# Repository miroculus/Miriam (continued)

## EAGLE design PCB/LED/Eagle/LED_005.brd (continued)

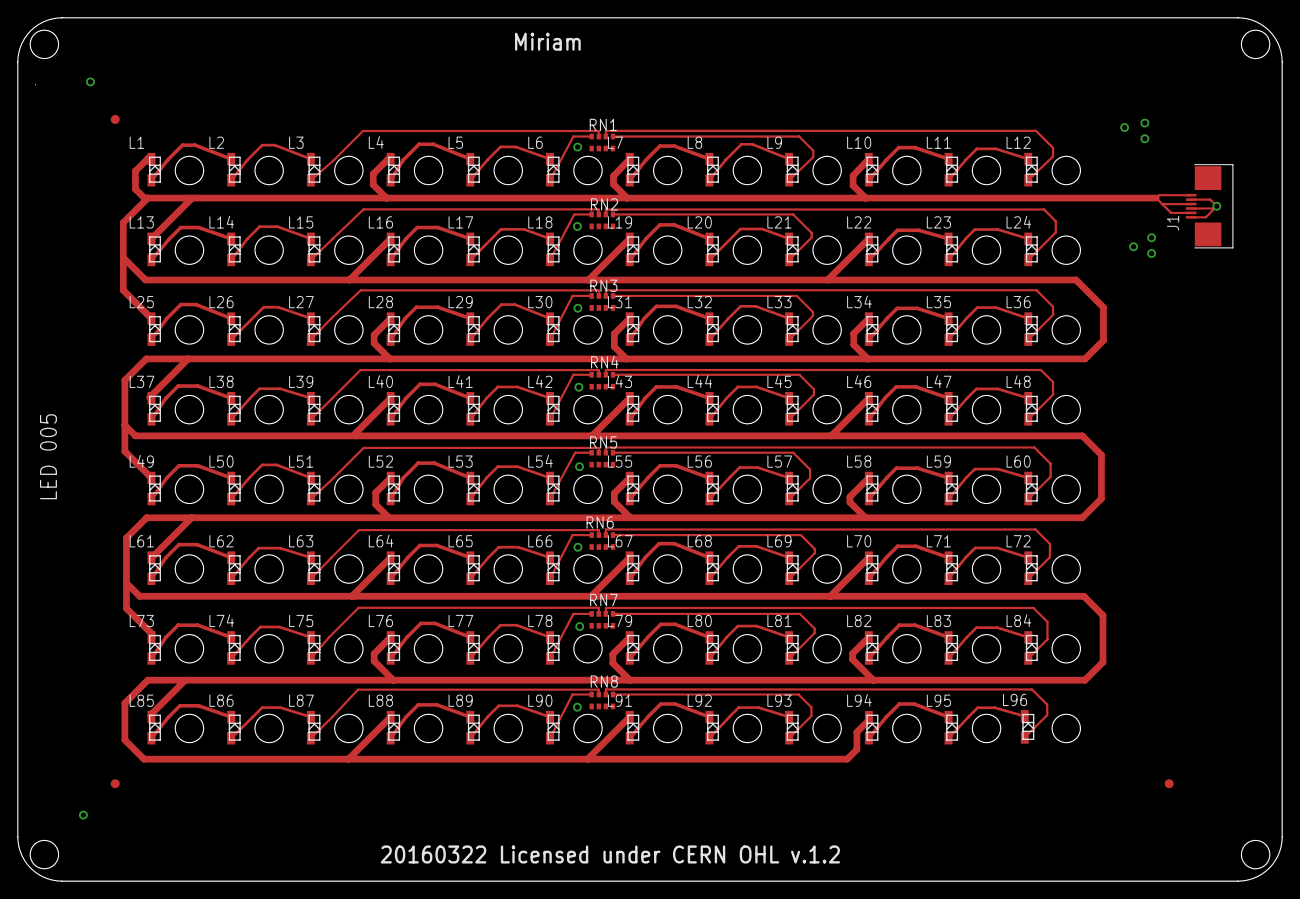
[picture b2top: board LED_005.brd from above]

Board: 2 copper layers, 142.8 x 97.5 mm, 108 parts (0 on the bottom side), 98 nets.

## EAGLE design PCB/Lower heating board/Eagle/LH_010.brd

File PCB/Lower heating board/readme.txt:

The used board is aluminum

- 1oz copper
- 1.6 mm thick
- Leadfree HAL
- Black soldermask
- White silkscreen

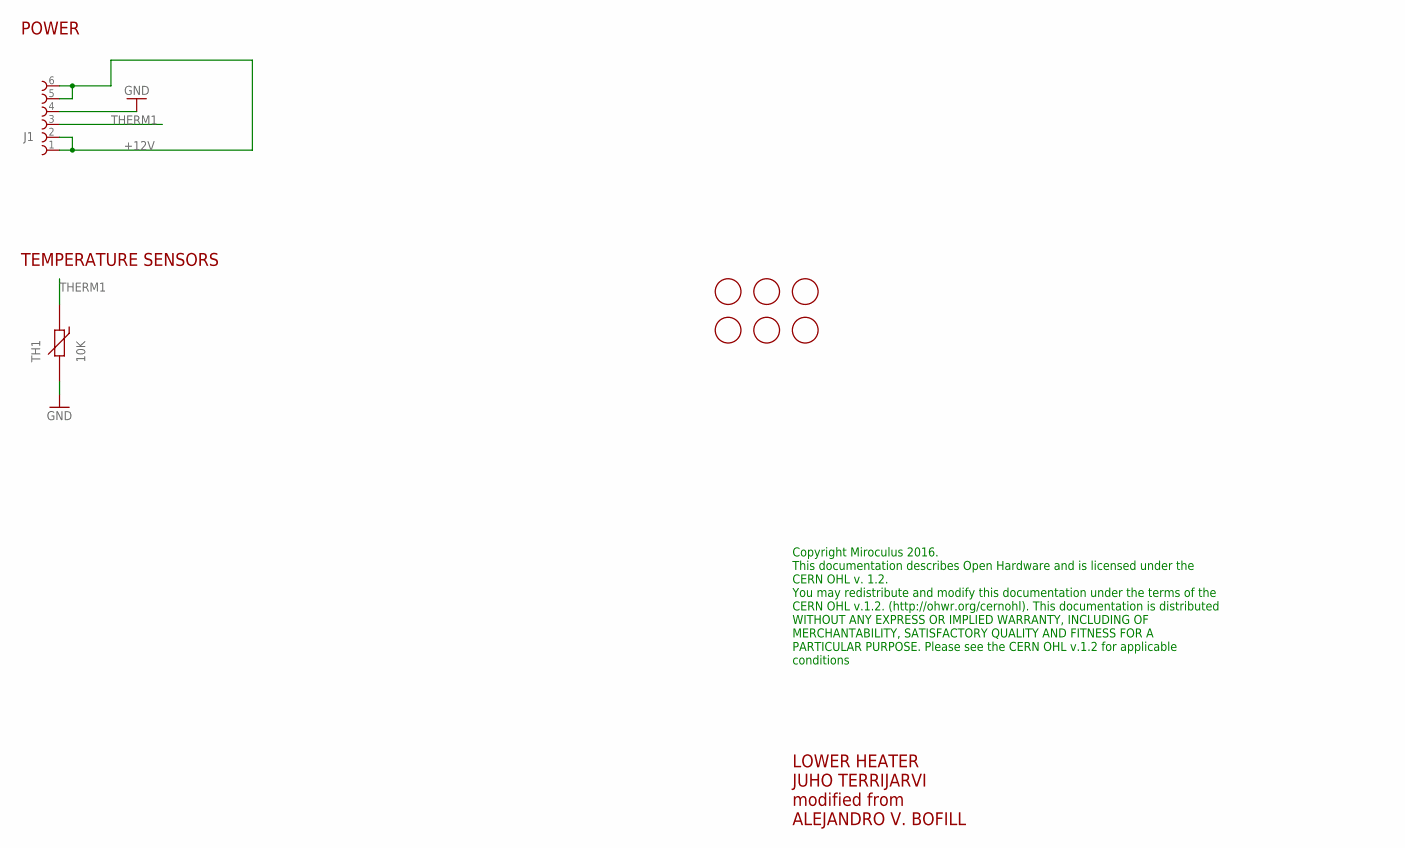
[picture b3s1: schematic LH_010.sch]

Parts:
FD1, FD2, FD3, FD4, FD5, FD6: FIDUCIALMOUNT; FIDUCIA-MOUNT
J1: 68710614522
TH1: 10K; THERMISTOR_SMD_0603

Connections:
+12V: J1.1, J1.2, J1.5, J1.6
GND: J1.4, TH1.2
THERM1: J1.3, TH1.1

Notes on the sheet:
LOWER HEATER JUHO TERRIJARVI modified from ALEJANDRO V. BOFILL
POWER
TEMPERATURE SENSORS
Copyright Miroculus 2016. This documentation describes Open Hardware and is licensed under the CERN OHL v. 1.2. You may redistribute and modify this documentation under the terms of the CERN OHL v.1.2. (http://ohwr.org/cernohl). This documentation is distributed WITHOUT ANY EXPRESS OR IMPLIED WARRA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

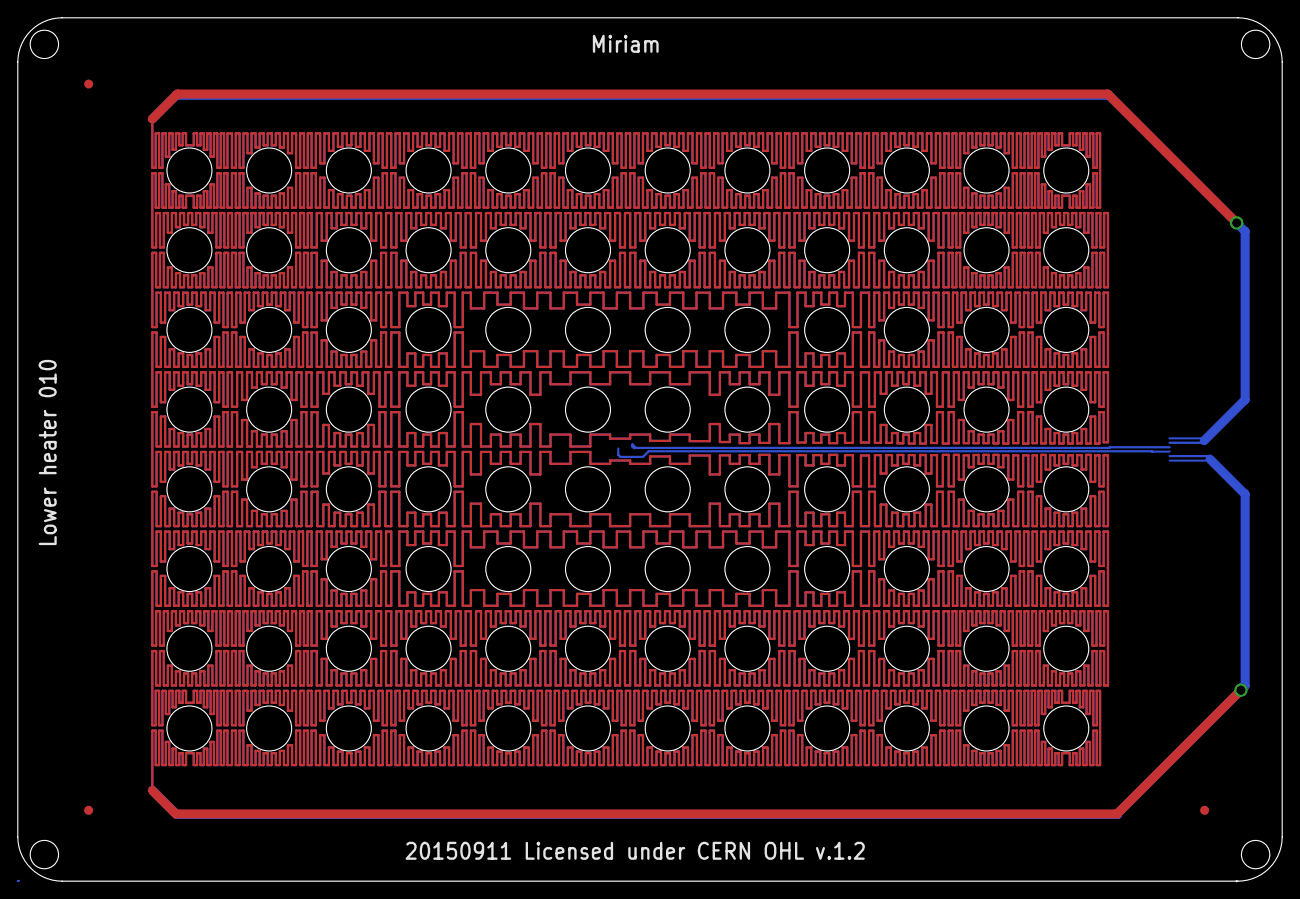
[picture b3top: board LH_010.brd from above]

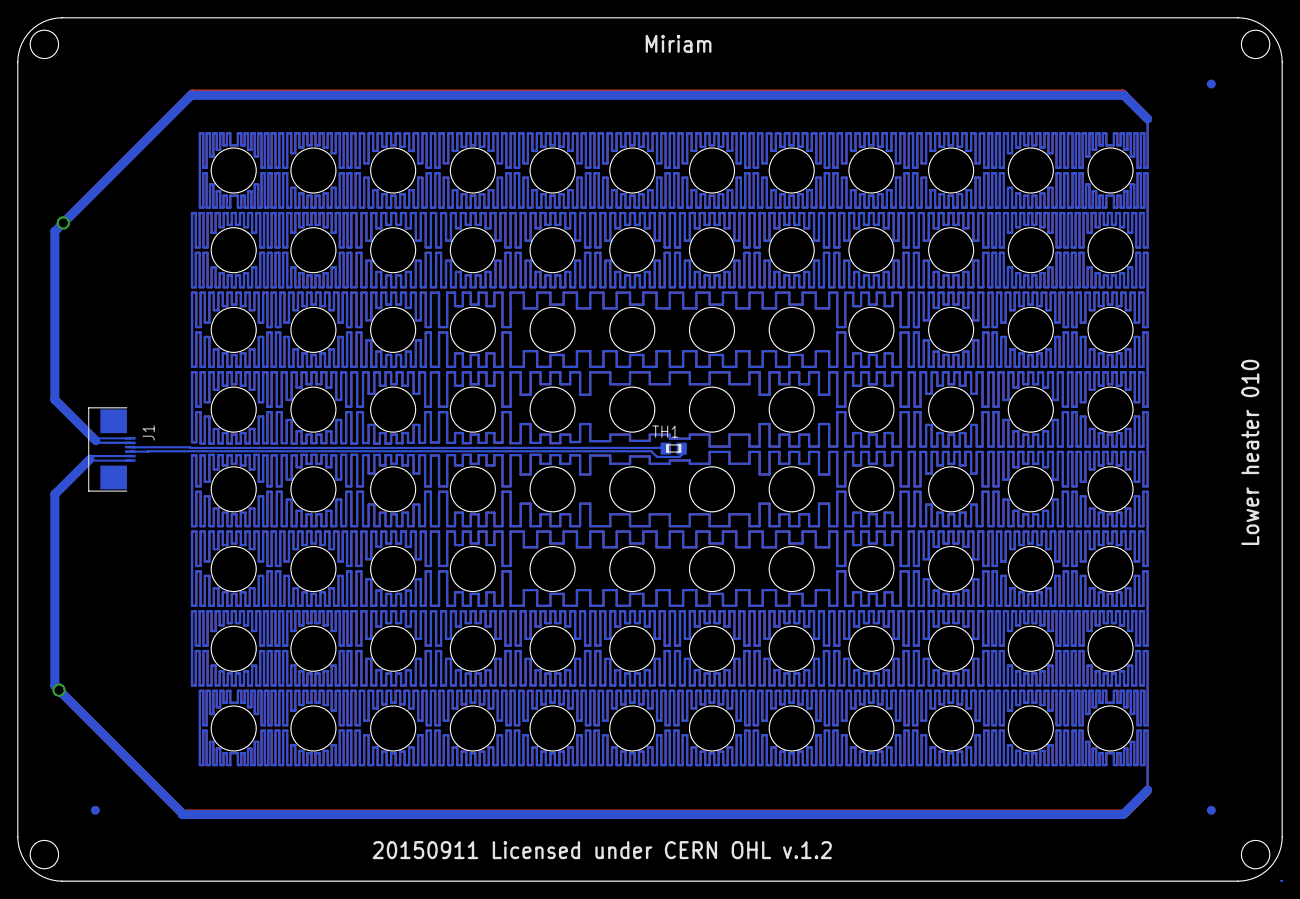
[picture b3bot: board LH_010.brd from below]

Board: 2 copper layers, 142.8 x 97.5 mm, 8 parts (5 on the bottom side), 3 nets.

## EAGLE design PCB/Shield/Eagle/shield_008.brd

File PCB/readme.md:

# PCBs

The PCBs have been drawn with Eagle software 7.3.0

PCB order details are in separate readme files in correct subfolders.

The Bills of material can be found under folder BOM. Datasheets of the main components are under folder Components.

Some of the component layouts can be found under Library folder that houses the Eagle .lbrs

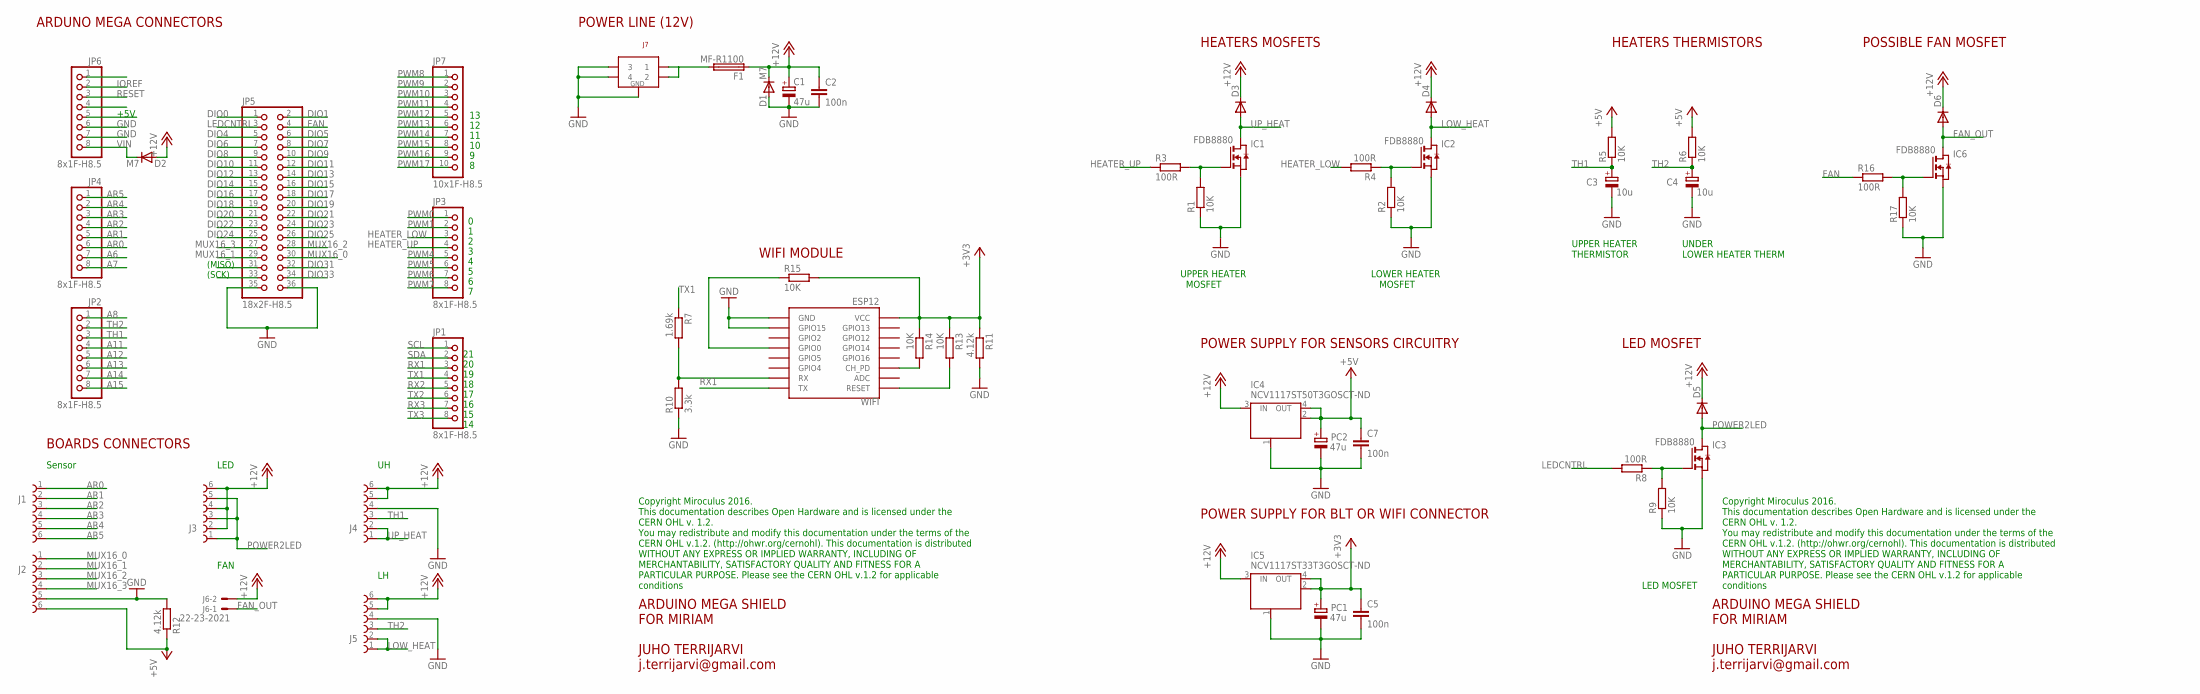
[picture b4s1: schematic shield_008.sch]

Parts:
C1: 47u; PANASONIC_D
C2, C5, C7: 100n; C0603
C3, C4: 10u; A/3216-18R
D1, D2: M7; SMB
D3, D4, D5, D6: RGL34A; DO-213AA_DIODE
F1: MF-R1100; LITTLEFUSE; FARNELL 1652183
IC1, IC2, IC3, IC6: FDB8880
IC4: NCV1117ST50T3GOSCT-ND; SOT223
IC5: NCV1117ST33T3GOSCT-ND; SOT223
J1, J2, J3, J4, J5: 68710614522
J6: 22-23-2021
J7: KPJX-4S-S
JP1, JP2, JP3, JP4, JP6: 8x1F-H8.5; 1X08
JP5: 18x2F-H8.5; 2X18
JP7: 10x1F-H8.5; 1X10
PC1, PC2: 47u; PANASONIC_D
R1, R2, R5, R6, R9, R13, R14, R15, R17: 10K; R0603
R3, R4, R8, R16: 100R; R0603
R7: 1.69k; R0603
R10: 3.3k; R0603
R11, R12: 4.12k; R0603
WIFI: ESP12

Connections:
+3V3: C5.1, IC5.2 (OUT), IC5.4 (OUT), PC1.+, R11.1, R13.1, R14.1, R15.2, WIFI.VCC
+5V: C7.1, IC4.2 (OUT), IC4.4 (OUT), J2.6, PC2.+, R5.2, R6.2, R12.1
+12V: C1.+, C2.1, D1.C, D2.A, D3.P$2 (C), D4.P$2 (C), D5.P$2 (C), D6.P$2 (C), F1.1, IC4.3 (IN), IC5.3 (IN), J3.2, J3.4, J3.6, J4.5, J4.6, J5.5, J5.6, J6.2
A6: JP4.7
A7: JP4.8
A8: JP2.1
A11: JP2.4
A12: JP2.5
A13: JP2.6
A14: JP2.7
A15: JP2.8
AR0: J1.1, JP4.6
AR1: J1.2, JP4.5
AR2: J1.3, JP4.4
AR3: J1.4, JP4.3
AR4: J1.5, JP4.2
AR5: J1.6, JP4.1
DIO0: JP5.1
DIO1: JP5.2
DIO4: JP5.5
DIO5: JP5.6
DIO6: JP5.7
DIO7: JP5.8
DIO8: JP5.9
DIO9: JP5.10
DIO10: JP5.11
DIO11: JP5.12
DIO12: JP5.13
DIO13: JP5.14
DIO14: JP5.15
DIO15: JP5.16
DIO16: JP5.17
DIO17: JP5.18
DIO18: JP5.19
DIO19: JP5.20
DIO20: JP5.21
DIO21: JP5.22
DIO22: JP5.23
DIO23: JP5.24
DIO24: JP5.25
DIO25: JP5.26
DIO30: JP5.31
DIO31: JP5.32
DIO32: JP5.33
DIO33: JP5.34
FAN: JP5.4, R16.1
FAN_OUT: D6.P$1 (A), IC6.2 (D), J6.1
GND: C1.-, C2.2, C3.-, C4.-, C5.2, C7.2, D1.A, IC1.3 (S), IC2.3 (S), IC3.3 (S), IC4.1 (GND/ADJ), IC5.1 (GND/ADJ), IC6.3 (S), J2.5, J4.4, J5.4, J7.P$3 (3), J7.P$4 (4), J7.P$5 (G), J7.P$6 (G), J7.P$7 (G), JP5.35, JP5.36, JP6.6, JP6.7, PC1.-, PC2.-, R1.1, R2.1, R9.1, R10.1, R11.2, R12.2, R17.1, WIFI.GND, WIFI.GPIO15
HEATER_LOW: JP3.3, R4.2
HEATER_UP: JP3.4, R3.1
IOREF: JP6.2
LEDCNTRL: JP5.3, R8.2
LOW_HEAT: D4.P$1 (A), IC2.2 (D), J5.1, J5.2
MUX16_0: J2.1, JP5.30
MUX16_1: J2.2, JP5.29
MUX16_2: J2.3, JP5.28
MUX16_3: J2.4, JP5.27
unnamed: IC3.1 (G), R8.1, R9.2
unnamed: R7.2, R10.2, WIFI.RX
unnamed: R13.2, WIFI.RESET
unnamed: R14.2, WIFI.CH_PD
unnamed: R15.1, WIFI.GPIO0
unnamed: F1.2, J7.P$1 (1), J7.P$2 (2)
unnamed: IC6.1 (G), R16.2, R17.2
unnamed: IC1.1 (G), R1.2, R3.2
unnamed: IC2.1 (G), R2.2, R4.1
POWER2LED: D5.P$1 (A), IC3.2 (D), J3.1, J3.3, J3.5
PWM0: JP3.1
PWM1: JP3.2
PWM4: JP3.5
PWM5: JP3.6
PWM6: JP3.7
PWM7: JP3.8
PWM8: JP7.1
PWM9: JP7.2
PWM10: JP7.3
PWM11: JP7.4
PWM12: JP7.5
PWM13: JP7.6
PWM14: JP7.7
PWM15: JP7.8
PWM16: JP7.9
PWM17: JP7.10
RESET: JP6.3
RX1: JP1.3, WIFI.TX
RX2: JP1.5
RX3: JP1.7
SCL: JP1.1
SDA: JP1.2
TH1: C3.+, J4.3, JP2.3, R5.1
TH2: C4.+, J5.3, JP2.2, R6.1
TX1: JP1.4, R7.1
TX2: JP1.6
TX3: JP1.8
UP_HEAT: D3.P$1 (A), IC1.2 (D), J4.1, J4.2
VIN: D2.C, JP6.8

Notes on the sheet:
(SCK)
(MISO)
ARDUNO MEGA CONNECTORS
ARDUINO MEGA SHIELD FOR MIRIAM JUHO TERRIJARVI j.terrijarvi@gmail.com
POWER LINE (12V)
BOARDS CONNECTORS
HEATERS MOSFETS
HEATERS THERMISTORS
UPPER HEATER THERMISTOR
UNDER LOWER HEATER THERM
UPPER HEATER MOSFET
LOWER HEATER MOSFET
WIFI MODULE
+5V
POWER SUPPLY FOR SENSORS CIRCUITRY
LED MOSFET
POWER SUPPLY FOR BLT OR WIFI CONNECTOR
Copyright Miroculus 2016. This documentation describes Open Hardware and is licensed under the CERN OHL v. 1.2. You may redistribute and modify this documentation under the terms of the CERN OHL v.1.2. (http://ohwr.org/cernohl). This documentation is distributed WITHOUT ANY EXPRESS OR IMPLIED WARRA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
Sensor
LED
POSSIBLE FAN MOSFET
FAN

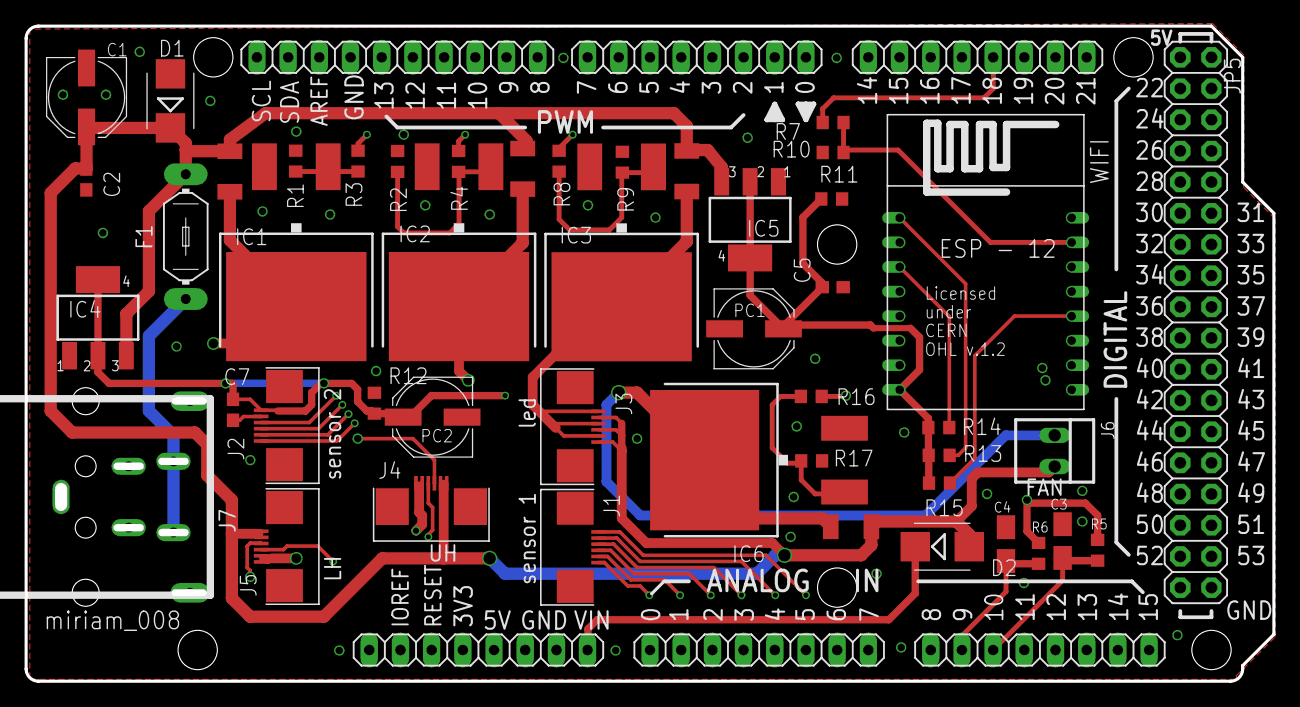
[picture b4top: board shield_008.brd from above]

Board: 4 copper layers, 101.6 x 53.3 mm, 53 parts (0 on the bottom side), 36 nets.

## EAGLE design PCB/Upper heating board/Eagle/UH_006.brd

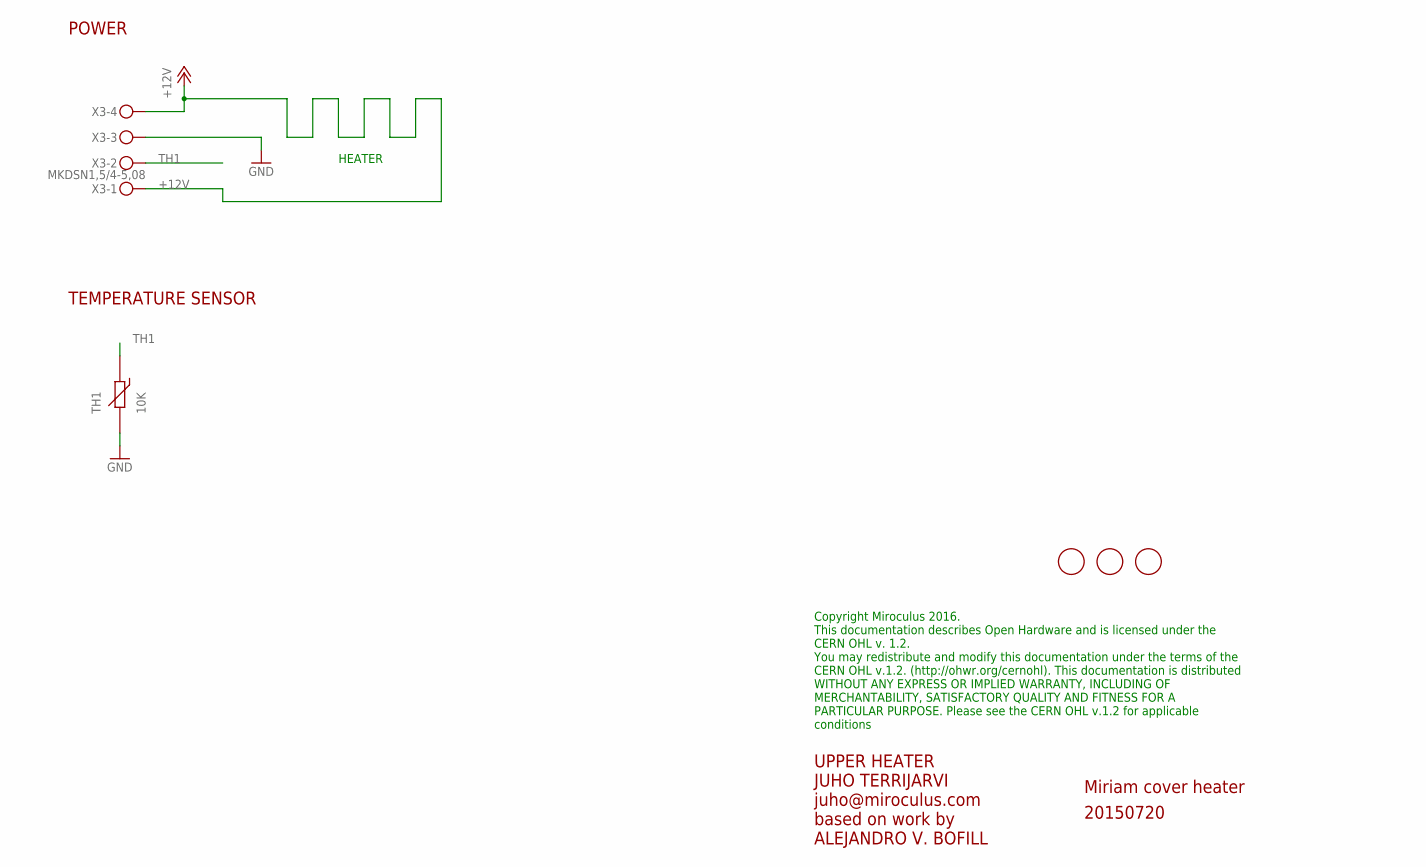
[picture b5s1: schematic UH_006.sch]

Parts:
FD1, FD2, FD3: FIDUCIALMOUNT; FIDUCIA-MOUNT
TH1: 10K; THERMISTOR_SMD_0603
X3: MKDSN1,5/4-5,08

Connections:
+12V: X3.1, X3.4
GND: TH1.2, X3.3
TH1: TH1.1, X3.2

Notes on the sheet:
POWER
UPPER HEATER JUHO TERRIJARVI juho@miroculus.com based on work by ALEJANDRO V. BOFILL
HEATER
TEMPERATURE SENSOR
Miriam cover heater
20150720
Copyright Miroculus 2016. This documentation describes Open Hardware and is licensed under the CERN OHL v. 1.2. You may redistribute and modify this documentation under the terms of the CERN OHL v.1.2. (http://ohwr.org/cernohl). This documentation is distributed WITHOUT ANY EXPRESS OR IMPLIED WARRA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

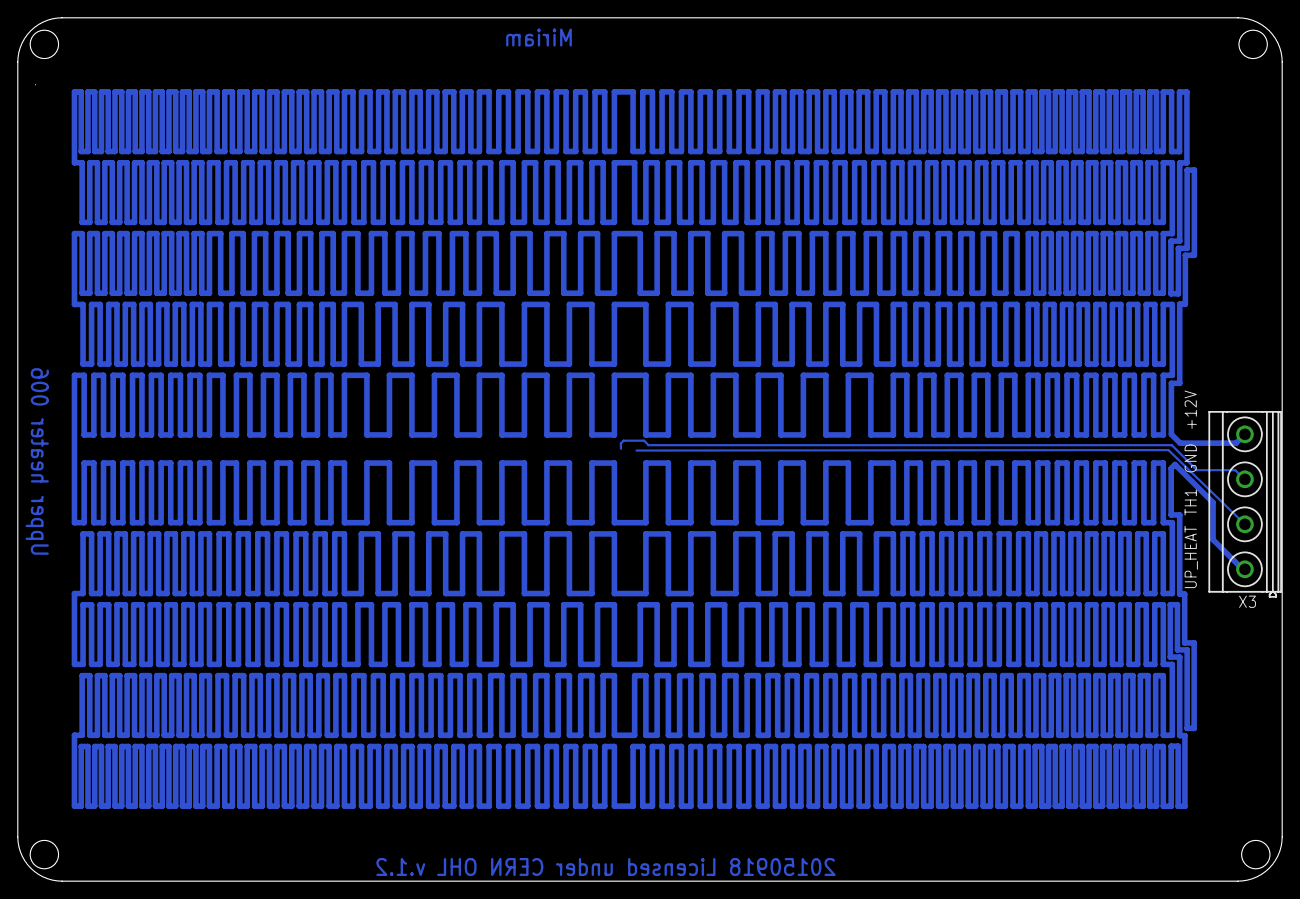
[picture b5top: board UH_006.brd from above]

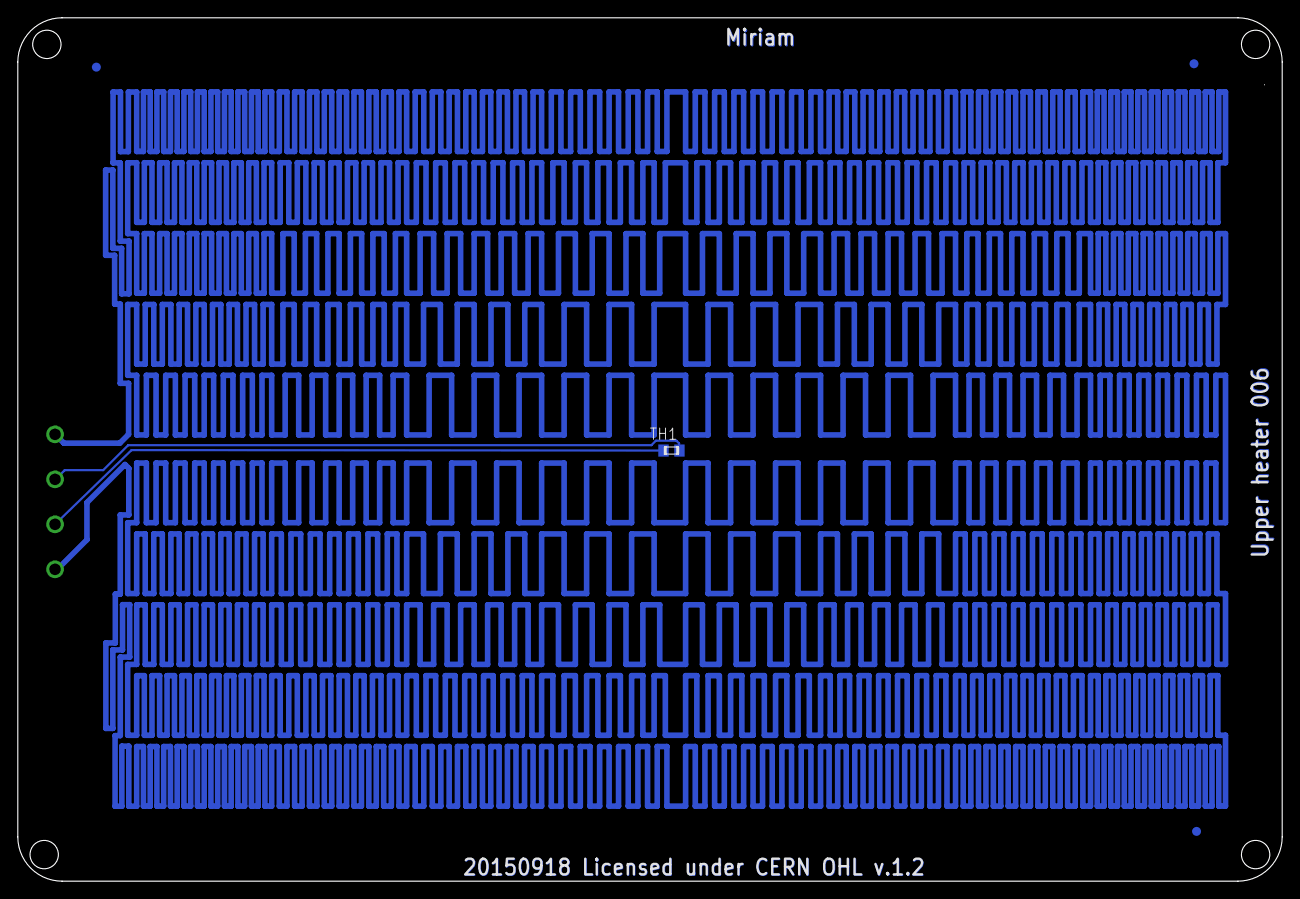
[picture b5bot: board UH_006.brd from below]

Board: 2 copper layers, 142.8 x 97.5 mm, 5 parts (4 on the bottom side), 3 nets.

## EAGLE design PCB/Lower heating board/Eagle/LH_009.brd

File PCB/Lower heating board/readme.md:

# LH_010

- material aluminum
- 2 layer
- single sided assembly
- 1oz copper
- 1.6 mm thick
- Leadfree HAL
- Black soldermask
- White silkscreen

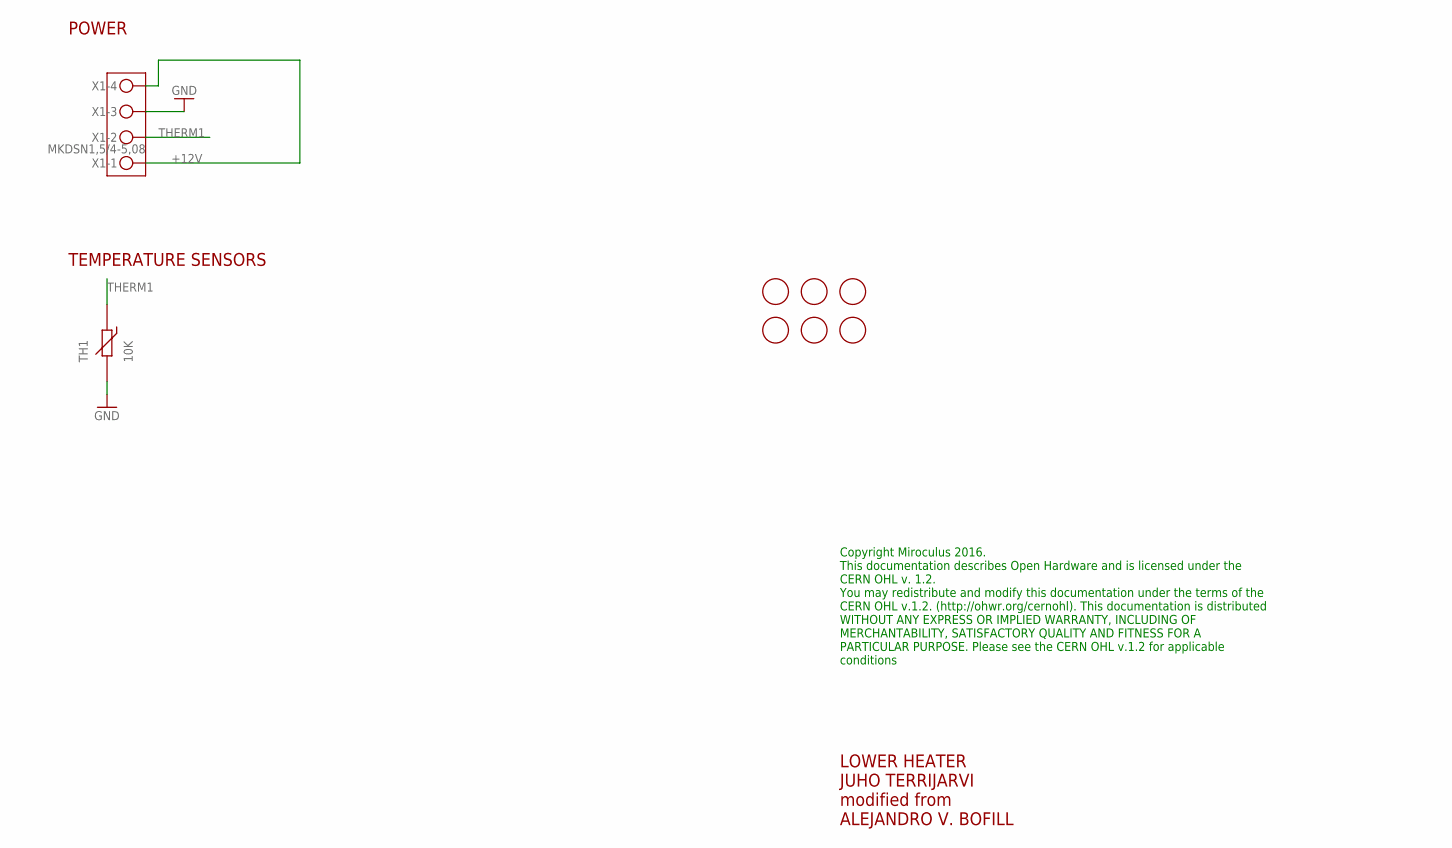
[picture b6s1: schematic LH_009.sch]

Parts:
FD1, FD2, FD3, FD4, FD5, FD6: FIDUCIALMOUNT; FIDUCIA-MOUNT
TH1: 10K; THERMISTOR_SMD_0603
X1: MKDSN1,5/4-5,08

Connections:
+12V: X1.1, X1.4
GND: TH1.2, X1.3
THERM1: TH1.1, X1.2

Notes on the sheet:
LOWER HEATER JUHO TERRIJARVI modified from ALEJANDRO V. BOFILL
POWER
TEMPERATURE SENSORS
Copyright Miroculus 2016. This documentation describes Open Hardware and is licensed under the CERN OHL v. 1.2. You may redistribute and modify this documentation under the terms of the CERN OHL v.1.2. (http://ohwr.org/cernohl). This documentation is distributed WITHOUT ANY EXPRESS OR IMPLIED WARRA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

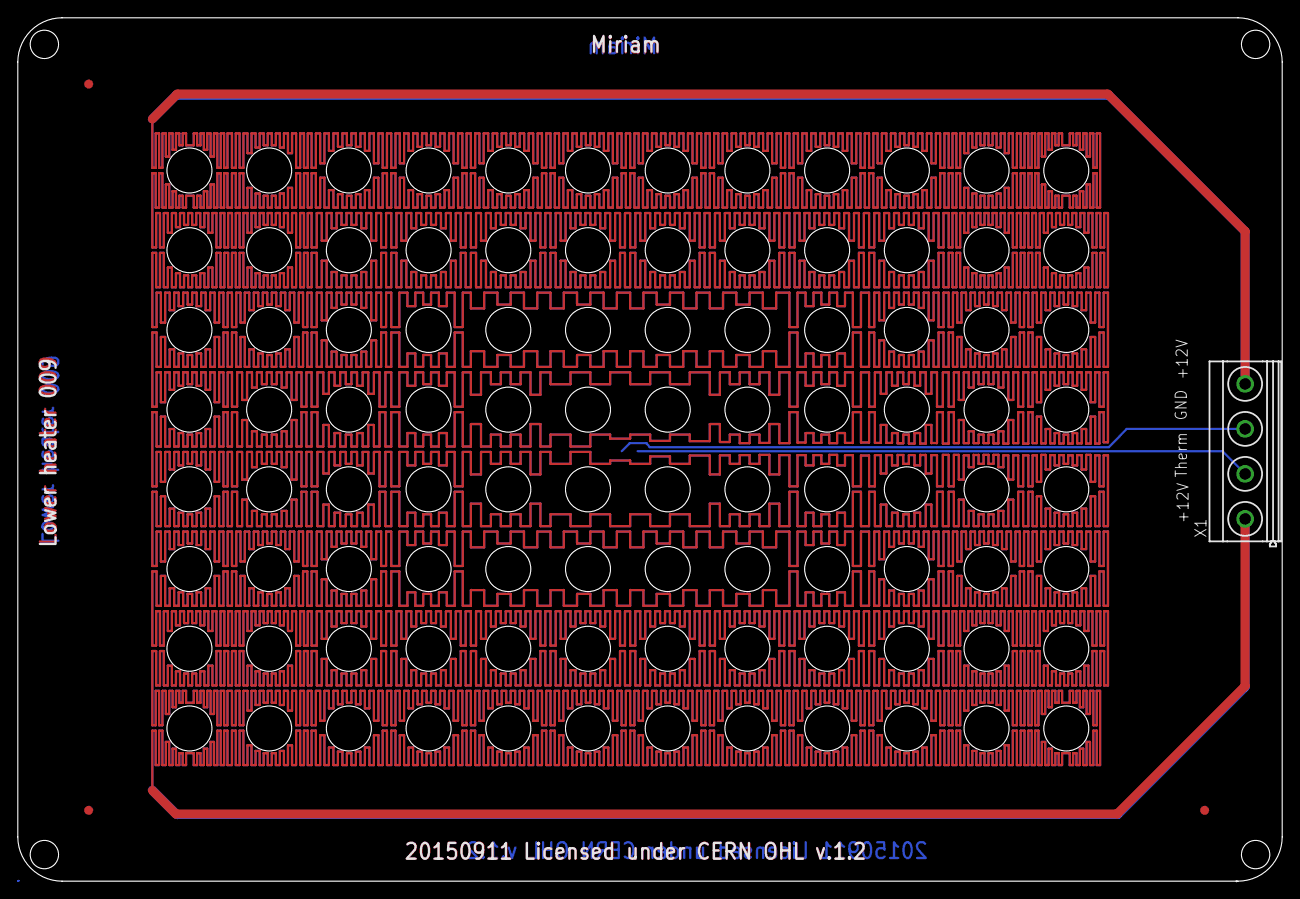
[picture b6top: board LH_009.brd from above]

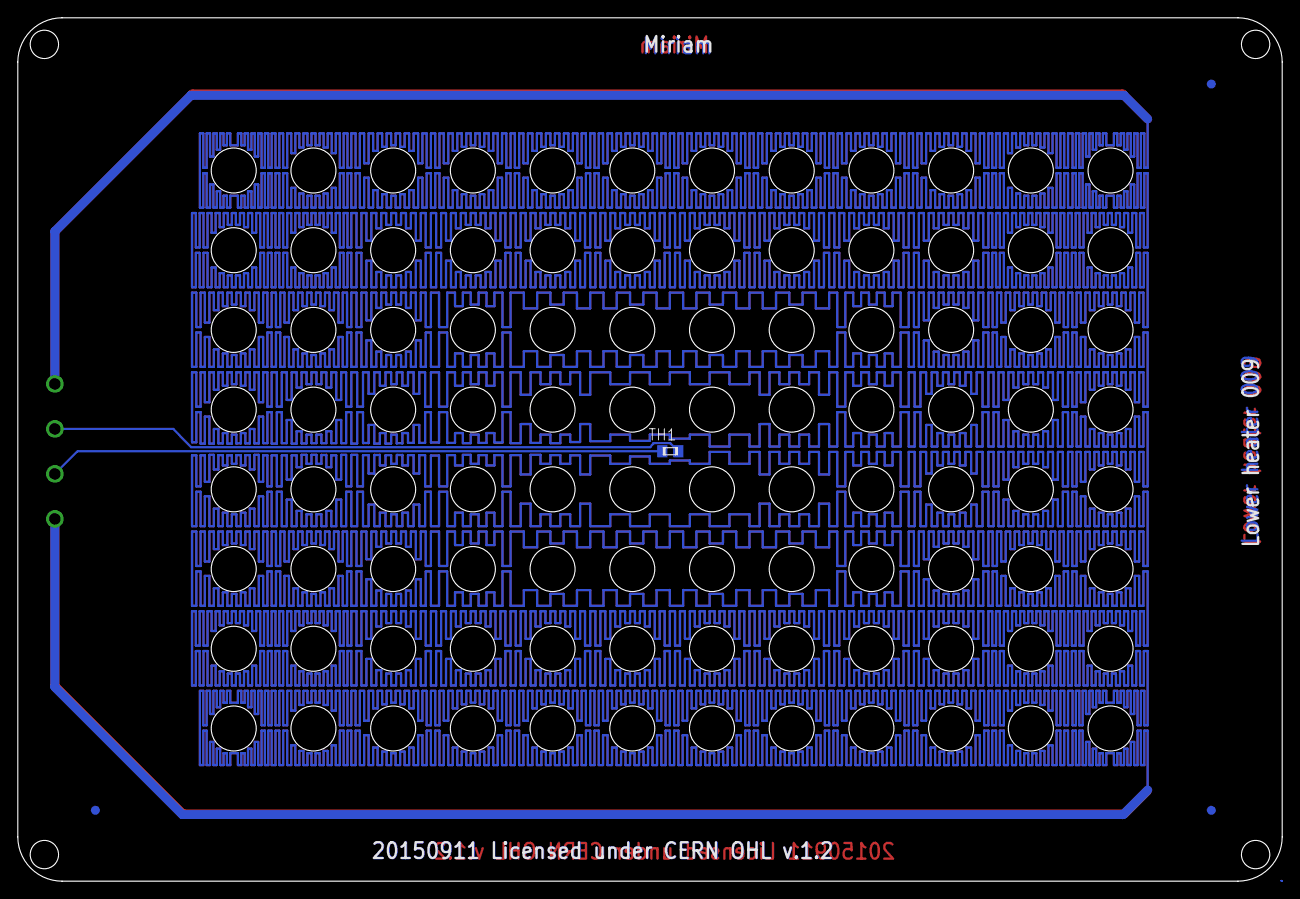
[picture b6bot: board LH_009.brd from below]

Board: 2 copper layers, 142.8 x 97.5 mm, 8 parts (4 on the bottom side), 3 nets.

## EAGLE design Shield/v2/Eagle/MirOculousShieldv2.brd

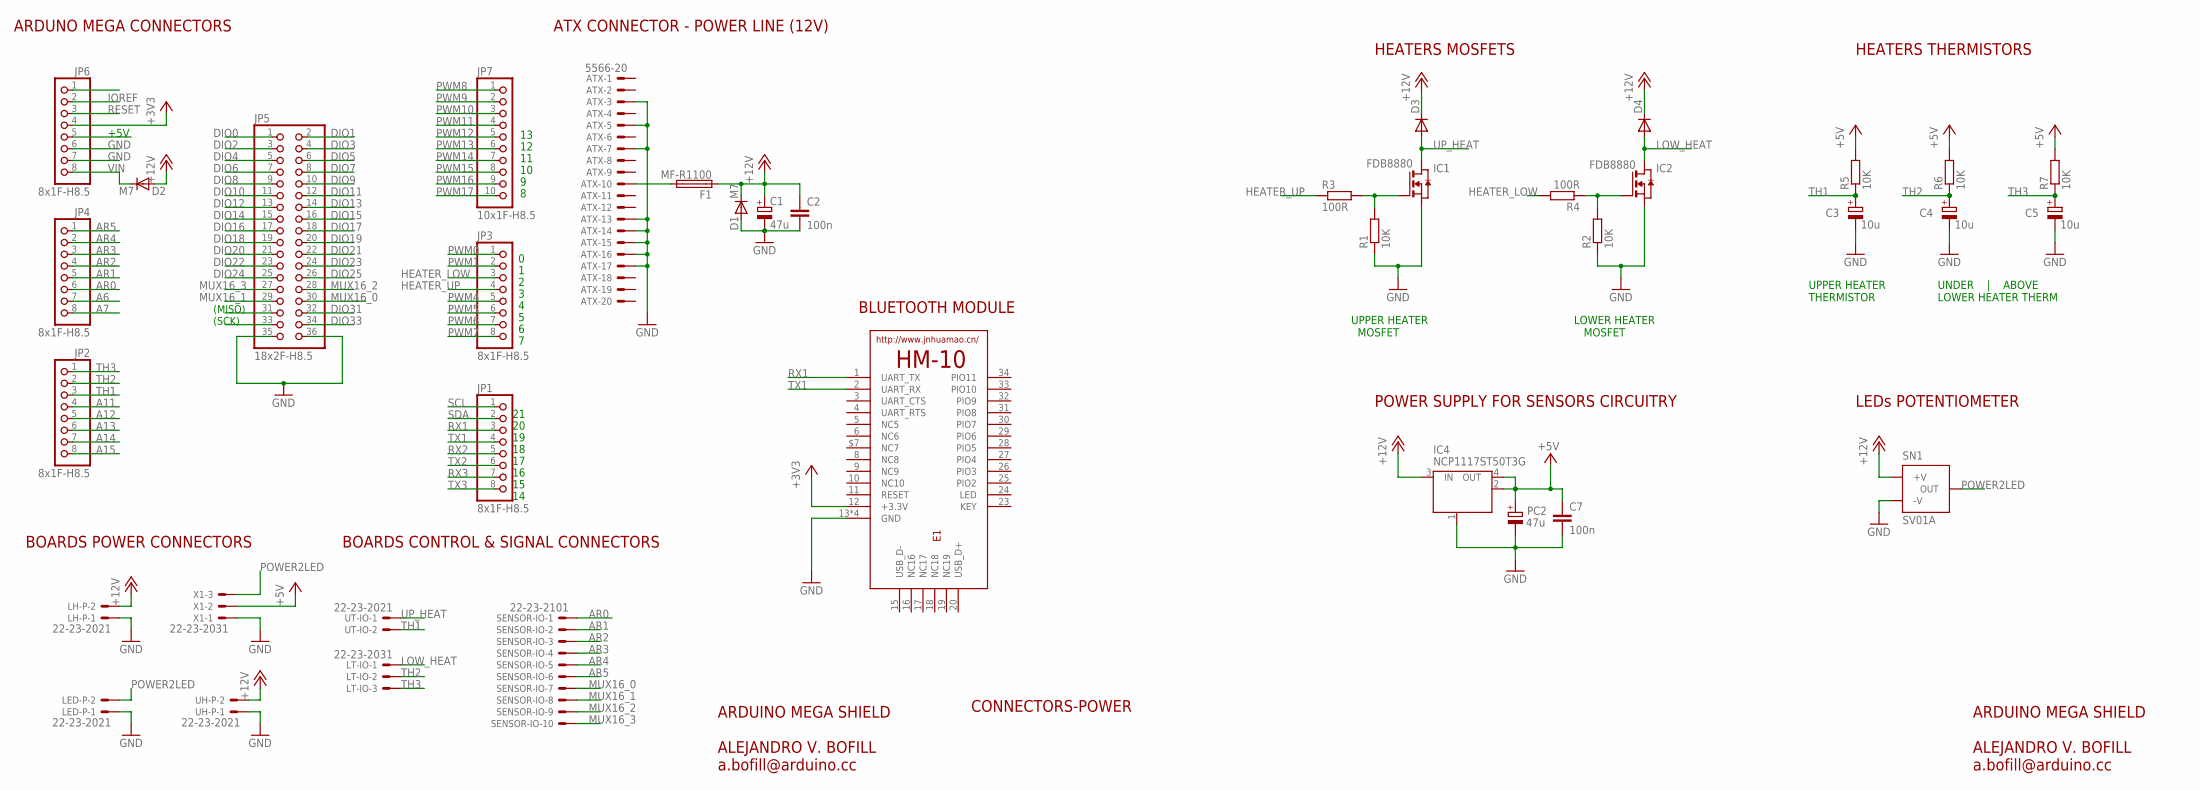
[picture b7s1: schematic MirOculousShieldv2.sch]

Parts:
ATX: 5566-20
C1: 47u; PANASONIC_D
C2, C7: 100n; C0603
C3, C4, C5: 10u; A/3216-18R
D1, D2: M7; SMB
D3, D4: RGL34A; DO-213AA_DIODE
E1: HM-10-BOARD; 26.9X13X2.2_BOARD
F1: MF-R1100; LITTLEFUSE; FARNELL 1652183
IC1, IC2: FDB8880
IC4: NCP1117ST50T3G; SOT223
JP1, JP2, JP3, JP4, JP6: 8x1F-H8.5; 1X08
JP5: 18x2F-H8.5; 2X18
JP7: 10x1F-H8.5; 1X10
LED-P: 22-23-2021
LH-P: 22-23-2021
LT-IO: 22-23-2031
PC2: 47u; PANASONIC_D
R1, R2, R5, R6, R7: 10K; R0603
R3, R4: 100R; R0603
SENSOR-IO: 22-23-2101
SN1: SV01A
UH-P: 22-23-2021
UT-IO: 22-23-2021
X1: 22-23-2031

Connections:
+3V3: E1.12 (+3.3V), JP6.4
+5V: C7.1, IC4.2 (OUT), IC4.4 (OUT), PC2.+, R5.2, R6.2, R7.2, X1.2
+12V: C1.+, C2.1, D1.C, D2.A, D3.P$2 (C), D4.P$2 (C), F1.1, IC4.3 (IN), LH-P.2, SN1.3 (+V), UH-P.2
A6: JP4.7
A7: JP4.8
A11: JP2.4
A12: JP2.5
A13: JP2.6
A14: JP2.7
A15: JP2.8
AR0: JP4.6, SENSOR-IO.1
AR1: JP4.5, SENSOR-IO.2
AR2: JP4.4, SENSOR-IO.3
AR3: JP4.3, SENSOR-IO.4
AR4: JP4.2, SENSOR-IO.5
AR5: JP4.1, SENSOR-IO.6
DIO0: JP5.1
DIO1: JP5.2
DIO2: JP5.3
DIO3: JP5.4
DIO4: JP5.5
DIO5: JP5.6
DIO6: JP5.7
DIO7: JP5.8
DIO8: JP5.9
DIO9: JP5.10
DIO10: JP5.11
DIO11: JP5.12
DIO12: JP5.13
DIO13: JP5.14
DIO14: JP5.15
DIO15: JP5.16
DIO16: JP5.17
DIO17: JP5.18
DIO18: JP5.19
DIO19: JP5.20
DIO20: JP5.21
DIO21: JP5.22
DIO22: JP5.23
DIO23: JP5.24
DIO24: JP5.25
DIO25: JP5.26
DIO30: JP5.31
DIO31: JP5.32
DIO32: JP5.33
DIO33: JP5.34
GND: ATX.3, ATX.5, ATX.7, ATX.13, ATX.14, ATX.15, ATX.16, ATX.17, C1.-, C2.2, C3.-, C4.-, C5.-, C7.2, D1.A, E1.13 (GND), E1.14 (GND), E1.21 (GND), E1.22 (GND), IC1.3 (S), IC2.3 (S), IC4.1 (GND/ADJ), JP5.35, JP5.36, JP6.6, JP6.7, LED-P.1, LH-P.1, PC2.-, R1.1, R2.1, SN1.1 (-V), UH-P.1, X1.1
HEATER_LOW: JP3.3, R4.2
HEATER_UP: JP3.4, R3.1
IOREF: JP6.2
LOW_HEAT: D4.P$1 (A), IC2.2 (D), LT-IO.1
MUX16_0: JP5.30, SENSOR-IO.7
MUX16_1: JP5.29, SENSOR-IO.8
MUX16_2: JP5.28, SENSOR-IO.9
MUX16_3: JP5.27, SENSOR-IO.10
unnamed: ATX.10, F1.2
unnamed: IC1.1 (G), R1.2, R3.2
unnamed: IC2.1 (G), R2.2, R4.1
POWER2LED: LED-P.2, SN1.2 (OUT), X1.3
PWM0: JP3.1
PWM1: JP3.2
PWM4: JP3.5
PWM5: JP3.6
PWM6: JP3.7
PWM7: JP3.8
PWM8: JP7.1
PWM9: JP7.2
PWM10: JP7.3
PWM11: JP7.4
PWM12: JP7.5
PWM13: JP7.6
PWM14: JP7.7
PWM15: JP7.8
PWM16: JP7.9
PWM17: JP7.10
RESET: JP6.3
RX1: E1.1 (UART_TX), JP1.3
RX2: JP1.5
RX3: JP1.7
SCL: JP1.1
SDA: JP1.2
TH1: C3.+, JP2.3, R5.1, UT-IO.2
TH2: C4.+, JP2.2, LT-IO.2, R6.1
TH3: C5.+, JP2.1, LT-IO.3, R7.1
TX1: E1.2 (UART_RX), JP1.4
TX2: JP1.6
TX3: JP1.8
UP_HEAT: D3.P$1 (A), IC1.2 (D), UT-IO.1
VIN: D2.C, JP6.8

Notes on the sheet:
(SCK)
(MISO)
ARDUNO MEGA CONNECTORS
ARDUINO MEGA SHIELD ALEJANDRO V. BOFILL a.bofill@arduino.cc
CONNECTORS-POWER
ATX CONNECTOR - POWER LINE (12V)
BOARDS POWER CONNECTORS
BOARDS CONTROL & SIGNAL CONNECTORS
HEATERS MOSFETS
HEATERS THERMISTORS
UPPER HEATER THERMISTOR
UNDER | ABOVE LOWER HEATER THERM
UPPER HEATER MOSFET
LOWER HEATER MOSFET
BLUETOOTH MODULE
+5V
POWER SUPPLY FOR SENSORS CIRCUITRY
LEDs POTENTIOMETER

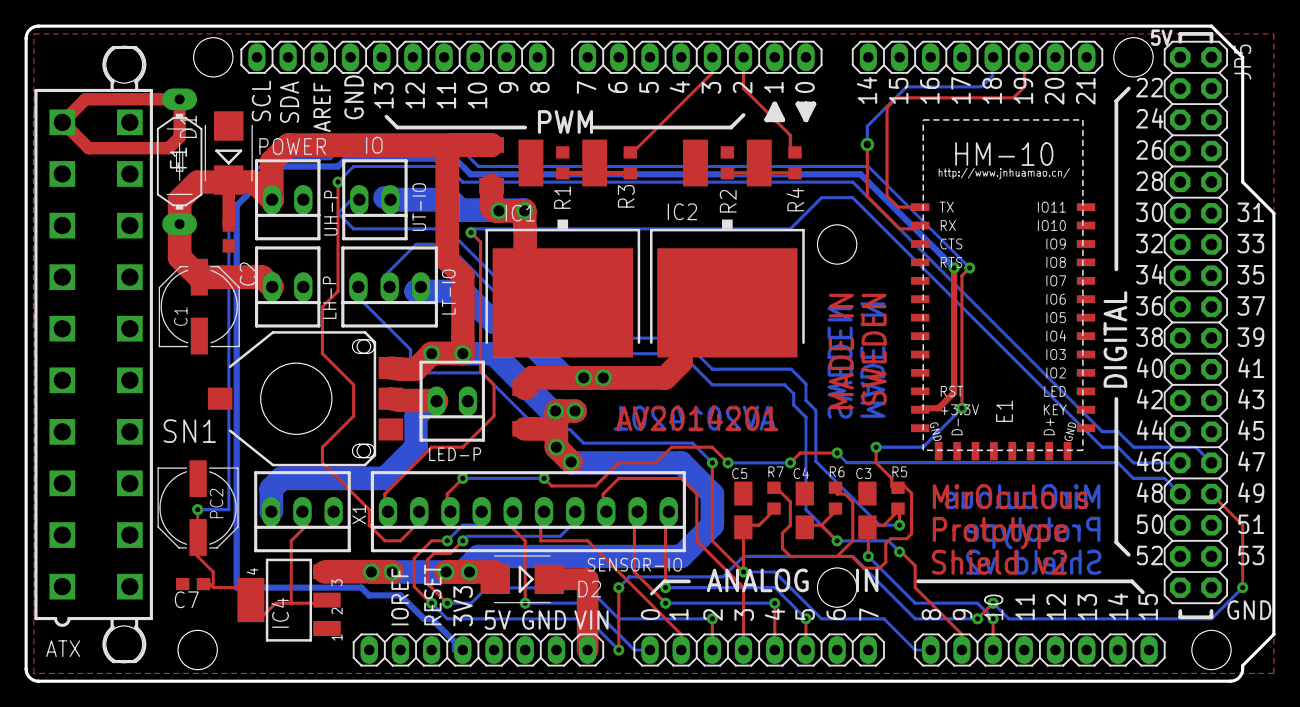
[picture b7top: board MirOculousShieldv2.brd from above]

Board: 2 copper layers, 101.6 x 53.3 mm, 39 parts (0 on the bottom side), 28 nets.

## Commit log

2016-02-05 previous shield
2016-02-12 3d files
2016-03-15 Update readme with dye
2016-03-15 Create publishable version
2016-03-15 Modify readme
2016-03-16 Setting up for launch
2016-03-16 Finish the programs, add GNU license
2016-03-22 PCB modification, CERN license
2016-03-22 License.md
2016-04-08 Updated PCB print details
2016-04-28 A refenrence to blt
2016-06-05 Removed quotes
2016-08-03 readme
2016-08-09 updated images and links
2019-04-06 Updated branch
2019-04-07 Added picture of miriam
2019-04-24 Modification
2019-05-30 Modify readme and add thesis
2019-05-30 Changed thesis to a link
2020-03-28 Deleted ATX, Added new board to board connectors and a possilibity to add a fan
2020-03-29 few corrections
2020-12-07 README links to the strawlab/Miriam repository
    Thanks for all the work on Miriam! We think it is a very clever design
    with great potential.
    We have been working pretty heavily on it for the past months and have a
    number of improvements and validations. Since several of the issues we
    opened in the Miroculus repository were not addressed within a span of
    weeks, and as agreed via email with Miroculus employees, we have been
